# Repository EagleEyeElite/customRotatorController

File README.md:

# Satellite Receiver

Student project: custom rotor design for portable ground station. \
Members of this group:
- Conrad Klaus (code and electronics)
- Prabhpreet S. Data (mechanics, prototype)
- Nasser Mazraani (final design build)

\

## PCB design
The pcb is designed as a raspberry pi hat to drive the motors and sensors.\
\

## Code
Main features:
- Rotctl
- Multithreading
- Sensors: magnetic encoder, quadrature
encoder, switches
- Separate driver modules: h-bridge, i2c
multiplexer etc.
- Position monitoring

For further information: ./src/README.md or ./documentation

Code structure: \

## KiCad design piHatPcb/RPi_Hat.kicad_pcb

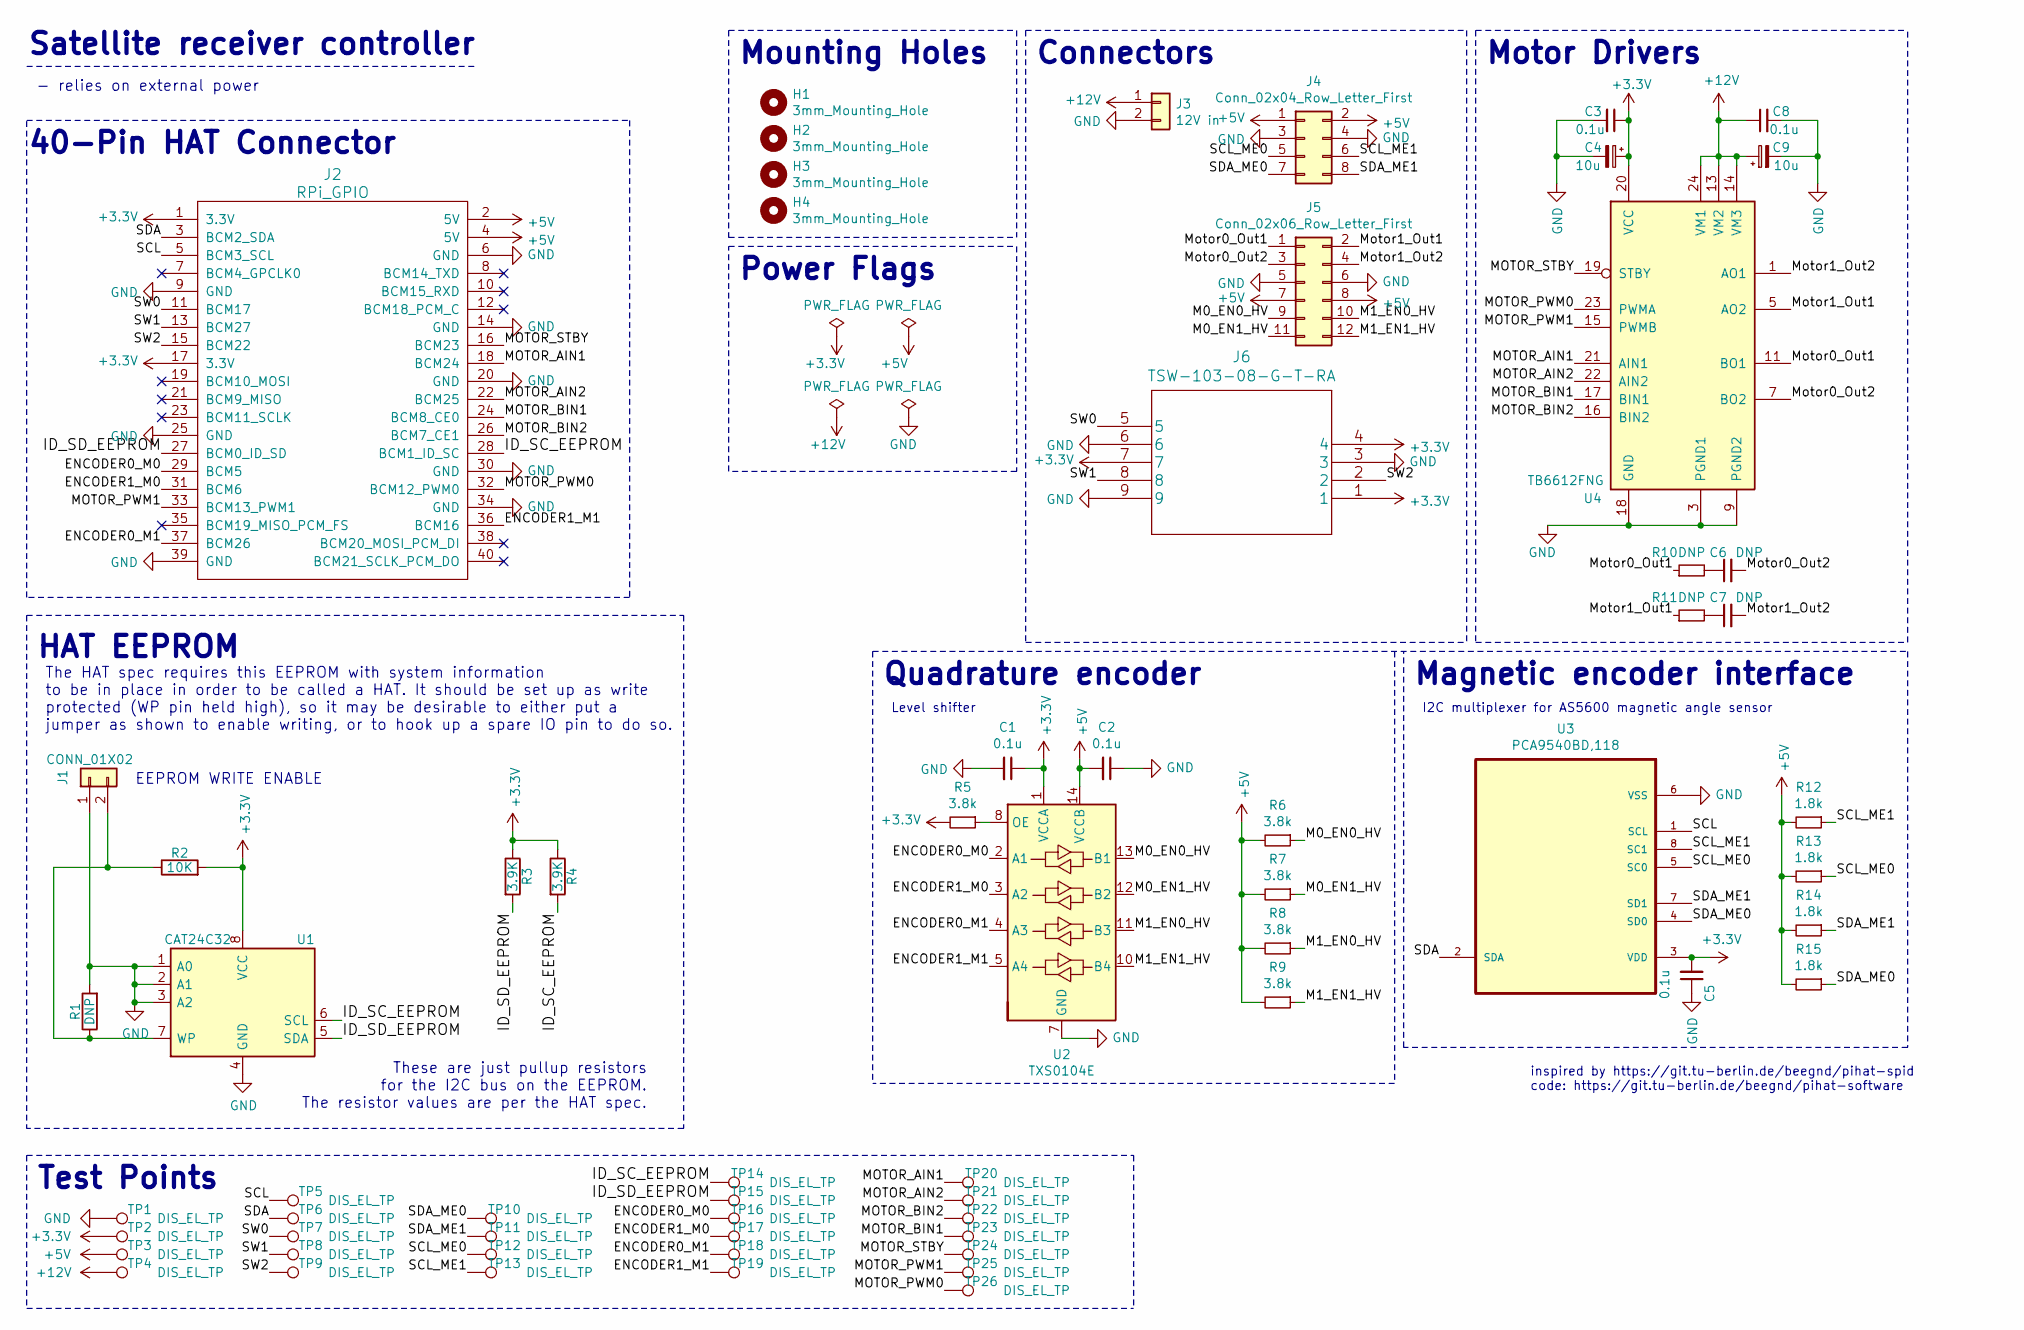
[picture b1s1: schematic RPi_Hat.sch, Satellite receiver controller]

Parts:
C1, C2, C3, C5, C8: 0.1u; C_0805_2012Metric_Pad1.18x1.45mm_HandSolder; Manufacturer_Part_Number 08055C104KAT2A; Digikey Part Number 478-1395-1-ND
C4, C9: 10u; C_0805_2012Metric_Pad1.18x1.45mm_HandSolder; Manufacturer_Part_Number CL21A106KOQNNNE; Digikey Part Number 1276-1096-2-ND
C6, C7: DNP; C_0805_2012Metric_Pad1.18x1.45mm_HandSolder
H1, H2, H3, H4: 3mm_Mounting_Hole; RPi_Hat_Mounting_Hole
J1: CONN_01X02; PinHeader_1x02_P2.54mm_Vertical; Manufacturer_Part_Number 77311-118-02LF; Digikey Part Number 609-4434-ND
J2: RPi_GPIO; PinSocket_2x20_P2.54mm_Vertical; Manufacturer_Part_Number 2222; Mouser Part Number 485-2222
J3: 12V in; PinHeader_1x02_P2.54mm_Horizontal; Manufacturer_Part_Number PH1RB-02-UA; Digikey Part Number 2057-PH1RB-02-UA-ND
J4: Conn_02x04_Row_Letter_First; PinHeader_2x04_P2.54mm_Horizontal; Manufacturer_Part_Number PH2RA-08-UA; Digikey Part Number 2057-PH2RA-08-UA-ND
J5: Conn_02x06_Row_Letter_First; PinHeader_2x06_P2.54mm_Horizontal; Manufacturer_Part_Number PH2RA-12-UA; Digikey Part Number 2057-PH2RA-12-UA-ND
J6: TSW-103-08-G-T-RA; Manufacturer_Part_Number TSW-103-08-G-T-RA; Digikey Part Number SAM8888-ND
R1, R10, R11: DNP; R_0805_2012Metric_Pad1.20x1.40mm_HandSolder
R2: 10K; R_0805_2012Metric_Pad1.20x1.40mm_HandSolder; Manufacturer_Part_Number CRCW080510K0FKEAC; Digikey Part Number 541-3976-1-ND
R3, R4: 3.9K; R_0805_2012Metric_Pad1.20x1.40mm_HandSolder; Manufacturer_Part_Number ERA-6AED392V; Digikey Part Number P123844CT-ND
R5, R6, R7, R8, R9: 3.8k; R_0805_2012Metric_Pad1.20x1.40mm_HandSolder; Manufacturer_Part_Number PAT0805E3791BST1; Digikey Part Number PAT3.79KBCT-ND
R12, R13, R14, R15: 1.8k; R_0805_2012Metric_Pad1.20x1.40mm_HandSolder; Manufacturer_Part_Number CRGCQ0805F1K8; Digikey Part Number A129752CT-ND
TP1, TP2, TP3, TP4, TP5, TP6, TP7, TP8, TP9, TP10, TP11, TP12, TP13, TP14, TP15, TP16, TP17, TP18, TP19, TP20, TP21, TP22, TP23, TP24, TP25, TP26: DIS_EL_TP; TestPoint_Pad_D1.0mm
U1: CAT24C32; SOIC-8_3.9x4.9mm_P1.27mm; Manufacturer_Part_Number CAT24C32WI-GT3; Digikey Part Number CAT24C32WI-GT3CT-ND
U2: TXS0104E; TSSOP-14_4.4x5mm_P0.65mm; Manufacturer_Part_Number TXB0104PWR; Mouser Part Number 595-TXS0104ED
U3: PCA9540BD,118; SOIC127P600X175-8N; Manufacturer_Part_Number PCA9540BD,118; Digikey Part Number 568-1844-1-ND
U4: TB6612FNG; SSOP-24_5.3x8.2mm_P0.65mm; Manufacturer_Part_Number TB6612FNG,C,8,EL; Digikey Part Number TB6612FNGC8ELCT-ND

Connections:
+3V3: C1.1, C3.1, C4.1, C5.2, J2.1 (3.3V), J2.17 (3.3V), J6.1, J6.4, J6.7, R2.2, R3.1, R4.1, R5.2, TP2.1, U1.8 (VCC), U2.1 (VCCA), U3.3 (VDD), U4.20 (VCC)
+5V: C2.2, J2.2 (5V), J2.4 (5V), J4.1, J4.2, J5.7, J5.8, R6.2, R7.2, R8.2, R9.2, R12.2, R13.2, R14.2, R15.2, TP3.1, U2.14 (VCCB)
+12V: C8.1, C9.1, J3.1, TP4.1, U4.13 (VM2), U4.14 (VM3), U4.24 (VM1)
/ENCODER0_M0: J2.29 (BCM5), TP16.1, U2.2 (A1)
/ENCODER0_M1: J2.37 (BCM26), TP18.1, U2.4 (A3)
/ENCODER1_M0: J2.31 (BCM6), TP17.1, U2.3 (A2)
/ENCODER1_M1: J2.36 (BCM16), TP19.1, U2.5 (A4)
/ID_SC_EEPROM: J2.28 (BCM1_ID_SC), R4.2, TP14.1, U1.6 (SCL)
/ID_SD_EEPROM: J2.27 (BCM0_ID_SD), R3.2, TP15.1, U1.5 (SDA)
/M0_EN0_HV: J5.9, R6.1, U2.13 (B1)
/M0_EN1_HV: J5.11, R7.1, U2.12 (B2)
/M1_EN0_HV: J5.10, R8.1, U2.11 (B3)
/M1_EN1_HV: J5.12, R9.1, U2.10 (B4)
/MOTOR_AIN1: J2.18 (BCM24), TP20.1, U4.21 (AIN1)
/MOTOR_AIN2: J2.22 (BCM25), TP21.1, U4.22 (AIN2)
/MOTOR_BIN1: J2.24 (BCM8_CE0), TP23.1, U4.17 (BIN1)
/MOTOR_BIN2: J2.26 (BCM7_CE1), TP22.1, U4.16 (BIN2)
/MOTOR_PWM0: J2.32 (BCM12_PWM0), TP26.1, U4.23 (PWMA)
/MOTOR_PWM1: J2.33 (BCM13_PWM1), TP25.1, U4.15 (PWMB)
/MOTOR_STBY: J2.16 (BCM23), TP24.1, U4.19 (STBY)
/Motor0_Out1: J5.1, R10.1, U4.11 (BO1), U4.12 (BO1)
/Motor0_Out2: C6.2, J5.3, U4.7 (BO2), U4.8 (BO2)
/Motor1_Out1: J5.2, R11.1, U4.5 (AO2), U4.6 (AO2)
/Motor1_Out2: C7.2, J5.4, U4.1 (AO1), U4.2 (AO1)
/SCL: J2.5 (BCM3_SCL), TP5.1, U3.1 (SCL)
/SCL_ME0: J4.5, R13.1, TP12.1, U3.5 (SC0)
/SCL_ME1: J4.6, R12.1, TP13.1, U3.8 (SC1)
/SDA: J2.3 (BCM2_SDA), TP6.1, U3.2 (SDA)
/SDA_ME0: J4.7, R15.1, TP10.1, U3.4 (SD0)
/SDA_ME1: J4.8, R14.1, TP11.1, U3.7 (SD1)
/SW0: J2.11 (BCM17), J6.5, TP7.1
/SW1: J2.13 (BCM27), J6.8, TP8.1
/SW2: J2.15 (BCM22), J6.2, TP9.1
GND: C1.2, C2.1, C3.2, C4.2, C5.1, C8.2, C9.2, J1.1, J2.6 (GND), J2.9 (GND), J2.14 (GND), J2.20 (GND), J2.25 (GND), J2.30 (GND), J2.34 (GND), J2.39 (GND), J3.2, J4.3, J4.4, J5.5, J5.6, J6.3, J6.6, J6.9, R1.2, TP1.1, U1.1 (A0), U1.2 (A1), U1.3 (A2), U1.4 (GND), U2.7 (GND), U3.6 (VSS), U4.3 (PGND1), U4.4 (PGND1), U4.9 (PGND2), U4.10 (PGND2), U4.18 (GND)
unnamed: C6.1, R10.2
unnamed: C7.1, R11.2
unnamed: J1.2, R1.1, R2.1, U1.7 (WP)
unnamed: R5.1, U2.8 (OE)

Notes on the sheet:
inspired by https://git.tu-berlin.de/beegnd/pihat-spid code: https://git.tu-berlin.de/beegnd/pihat-software
Motor Drivers
40-Pin HAT Connector
Connectors
Mounting Holes
Satellite receiver controller
- relies on external power
I2C multiplexer for AS5600 magnetic angle sensor
Quadrature encoder
Level shifter
Magnetic encoder interface
These are just pullup resistors for the I2C bus on the EEPROM. The resistor values are per the HAT spec.
The HAT spec requires this EEPROM with system information to be in place in order to be called a HAT. It should be set up as write protected (WP pin held high), so it may be desirable to either put a jumper as shown to enable writing, or to hook up a spare IO pin to do so.
HAT EEPROM
EEPROM WRITE ENABLE
Test Points
Power Flags

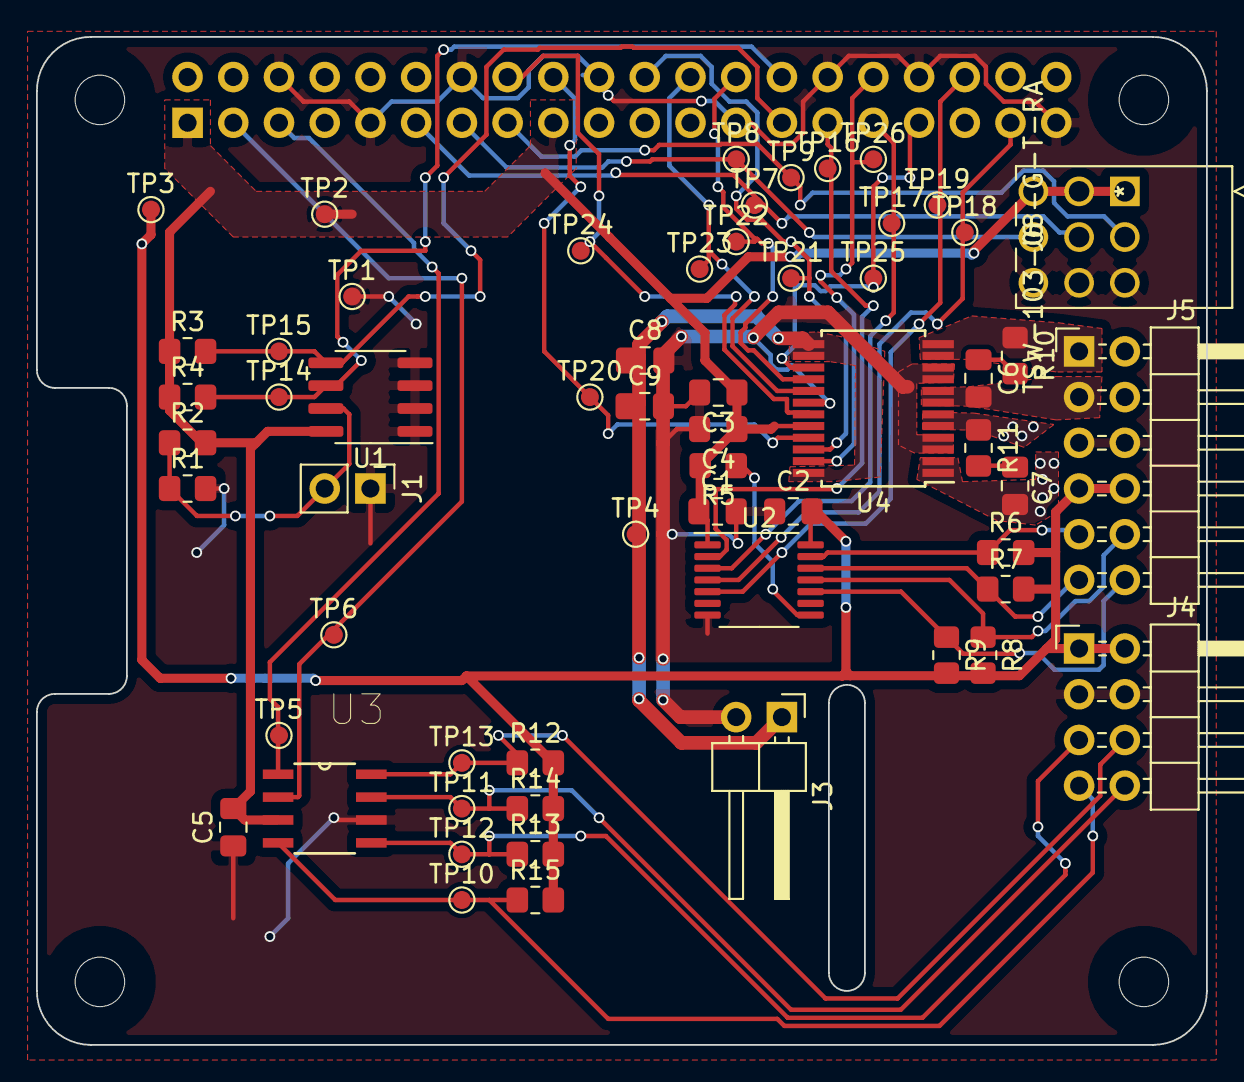
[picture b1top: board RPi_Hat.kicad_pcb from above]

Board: 2 copper layers, 65.0 x 56.0 mm, 64 parts (1 on the bottom side), 38 nets.

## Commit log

2021-05-15 add raspi conf
2021-05-15 add basic breadboard hBridge controller
2021-05-16 update hBridge
2021-05-24 set motor speed and direction
2021-05-24 add control for two motors
2021-05-24 add simple PID
2021-05-24 readout motor encoder
2021-05-24 add pid and direction controll
2021-05-24 separate classes
2021-05-27 use encoder direction and absolute position (demo included)
2021-05-27 include dependencies
2021-06-07 include pi hat template
2021-06-07 simplify and adjust template
2021-06-11 add pi HAT schematic (spid hat as template)
2021-06-11 add rough pcb layout
2021-06-21 finalize PCB layout
2021-06-21 adjust compontens, add BOM
2021-07-15 include pcb features: i2c, magnetic encoder, hBridge subdivide code into driver and control logic update pins to pcb remove pid control example code: monitor motor rotation
2021-07-16 add switch driver
2021-07-22 add simple rotctl service
2021-07-24 improve position management
2021-07-24 include all rotctl functions separation in packages first angle translator
2021-07-24 exit rotctl socket automatic, clean up, start rotator abstraction
2021-07-25 simplify configuration, move logic into Rotator Controller
2021-07-25 rename structure, move getAngle to shaft
2021-07-25 split position into receiver pos and shaft pos
2021-08-09 add comments
2021-08-09 add documentation template
2021-08-10 add sebastian report template with first content
2021-08-11 add pictures, diagrams and rough layout
2021-08-13 add full documentation for review

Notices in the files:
parts and their libraries:
Copyright 2021 Accelerated Designs. All rights reserved.
